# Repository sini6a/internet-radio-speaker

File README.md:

# Open Source Internet Radio Player

## Hardware Specifications

- **Microcontroller:** ESP32-C3
- **Power Supply:** 5V/0.5A (USB Type-C, ~2.5W)
- **Flash Memory:** 4Mbit QSPI (on-chip)
- **Antenna:** Integrated PCB antenna
- **Controls:** Power switch and analog volume potentiometer
- **Audio Output:** Dual speaker output (3.2W max per channel)
- **Indicators:** 3x LEDs (Wi-Fi, Playback, Power)

## Description

This project is a compact, ESP32-C3-based Internet Radio Player designed for ease of use and straightforward integration. The device supports Wi-Fi streaming of MP3 audio and includes basic control via a single potentiometer and button. Audio output is handled via I2S to a stereo amplifier. 

The hardware includes onboard status LEDs and is powered via USB Type-C. It's suitable for low-power audio streaming applications, DIY audio projects, or integration into custom enclosures.

## Features

- 2.4 GHz Wi-Fi support using the built-in PCB antenna
- Minimal controls for simple user interaction
- USB Type-C programming and power interface
- Stereo speaker output via digital I2S
- LED indicators for connection and playback status

## Firmware and Usage

The firmware is located in the `Firmware/` directory and is built using the Arduino framework. Upload it via the Arduino IDE or other compatible tools. 

### Initial Setup

1. Flash the firmware to the ESP32-C3.
2. On first boot, the device creates a Wi-Fi Access Point.
3. Connect to the AP to configure the Wi-Fi credentials and stream URL.
4. After setup, the device reboots into streaming mode.

## Status

- Current hardware revision is stable and has been tested.
- The device is functional and ready for personal assembly or integration.
- Further development (BLE config, web UI, OTA, etc.) is planned or ongoing.

## Contributions

Pull requests, issue reports, and improvements are welcome. Make sure to open issue before to discuss changes.

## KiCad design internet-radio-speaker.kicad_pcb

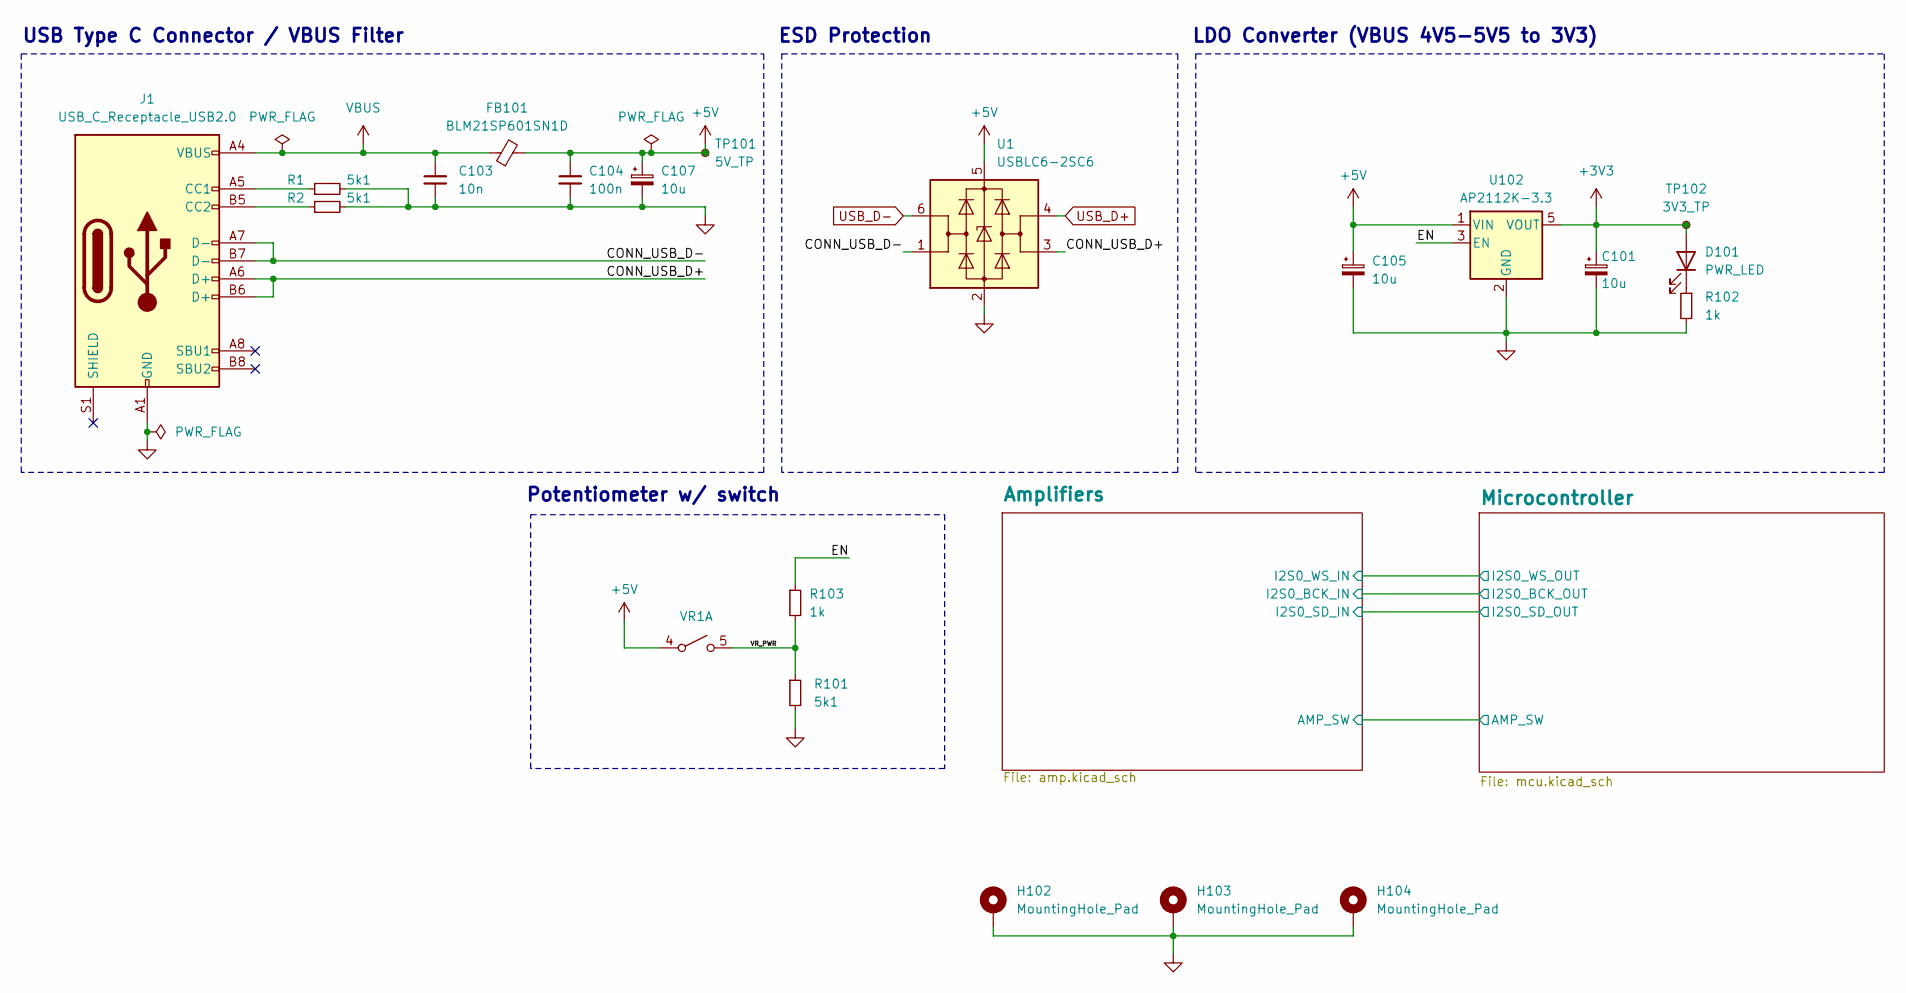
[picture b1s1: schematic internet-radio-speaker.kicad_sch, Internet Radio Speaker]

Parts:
C101, C105, C107: 10u; C_0603_1608Metric; JLCPCB Part # C96446
C103: 10n; C_0402_1005Metric; JLCPCB Part # C15195
C104: 100n; C_0402_1005Metric; JLCPCB Part # C1525
D101: PWR_LED; LED_0603_1608Metric; JLCPCB Part # C2286
FB101: BLM21SP601SN1D; L_0805_2012Metric; JLCPCB Part # C3716677
H102, H103, H104: MountingHole_Pad; MountingHole_2.7mm_M2.5_Pad_Via
J1: USB_C_Receptacle_USB2.0; USB_C_Receptacle_GCT_USB4105-xx-A_16P_TopMnt_Horizontal; JLCPCB Part # C2927038
R1, R2, R101: 5k1; R_0402_1005Metric; JLCPCB Part # C25905
R102, R103: 1k; R_0402_1005Metric; JLCPCB Part # C11702
TP101: 5V_TP; TestPoint_Pad_D1.5mm
TP102: 3V3_TP; TestPoint_Pad_D1.5mm
U1: USBLC6-2SC6; SOT-23-6; JLCPCB Part # C2687116
U102: AP2112K-3.3; SOT-23-5; JLCPCB Part # C51118
VR1: Potentiometer_Alps_RK0971111Z1P; JLCPCB Part # C2687318

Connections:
+3V3: C101.1, D101.2 (A), TP102.1, U102.5 (VOUT); also elsewhere on the board
+5V: C104.1, C105.1, C107.1, FB101.2, TP101.1, U1.5 (VBUS), U102.1 (VIN), VR1.4 (A); also elsewhere on the board
/CONN_USB_D+: J1.A6 (D+), J1.B6 (D+), U1.3 (I/O2)
/CONN_USB_D-: J1.A7 (D-), J1.B7 (D-), U1.1 (I/O1)
/EN: R103.1, U102.3 (EN)
/VR_PWR: R101.1, R103.2, VR1.5 (B)
GND: C101.2, C103.2, C104.2, C105.2, C107.2, H102.1, H103.1, H104.1, J1.A1 (GND), J1.A12 (GND), J1.B1 (GND), J1.B12 (GND), R1.2, R2.2, R101.2, R102.2, U1.2 (GND), U102.2 (GND); also elsewhere on the board
unnamed: D101.1 (K), R102.1
unnamed: J1.A5 (CC1), R1.1
unnamed: J1.B5 (CC2), R2.1
USB_D+: U1.4 (I/O2); also elsewhere on the board
USB_D-: U1.6 (I/O1); also elsewhere on the board
VBUS: C103.1, FB101.1, J1.A4 (VBUS), J1.A9 (VBUS), J1.B4 (VBUS), J1.B9 (VBUS)

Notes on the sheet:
ESD Protection
USB Type C Connector / VBUS Filter
Potentiometer w/ switch
LDO Converter (VBUS 4V5-5V5 to 3V3)

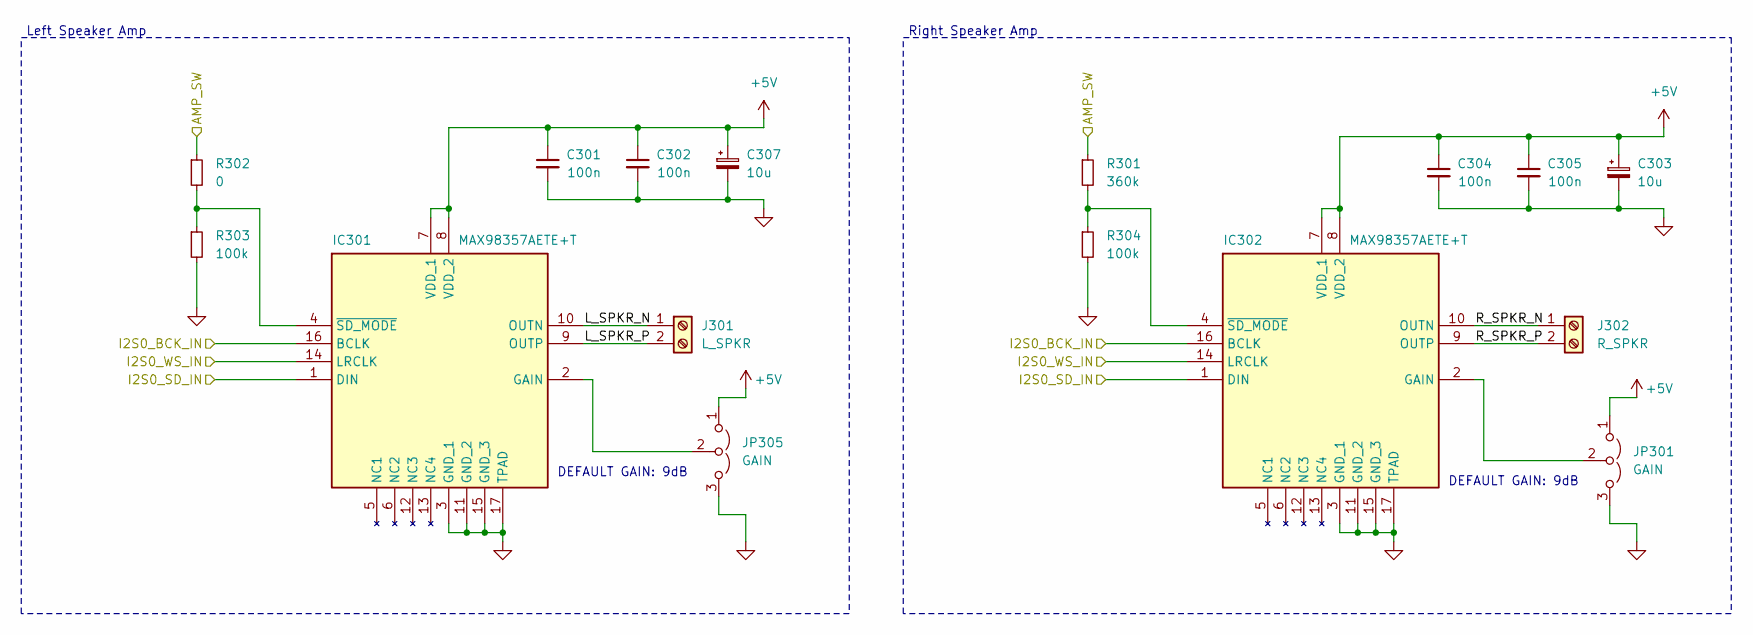
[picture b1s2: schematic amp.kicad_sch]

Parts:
C301, C302, C304, C305: 100n; C_0402_1005Metric; JLCPCB Part # C1525
C303, C307: 10u; C_0603_1608Metric; JLCPCB Part # C96446
IC301, IC302: MAX98357AETE+T; TQFN-16-1EP_3x3mm_P0.5mm_EP1.23x1.23mm_ThermalVias; JLCPCB Part # C910544
J301: L_SPKR; TerminalBlock_bornier-2_P5.08mm
J302: R_SPKR; TerminalBlock_bornier-2_P5.08mm
JP301, JP305: GAIN; SolderJumper-3_P1.3mm_Open_RoundedPad1.0x1.5mm
R301: 360k; R_0402_1005Metric; JLCPCB Part # C45956
R302: 0; R_0402_1005Metric; JLCPCB Part # C17168
R303, R304: 100k; R_0402_1005Metric; JLCPCB Part # C25741

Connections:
+5V: C301.1, C302.1, C303.1, C304.1, C305.1, C307.1, IC301.7 (VDD_1), IC301.8 (VDD_2), IC302.7 (VDD_1), IC302.8 (VDD_2), JP301.1 (A), JP305.1 (A); also elsewhere on the board
/Amplifiers/AMP_SW: R301.1, R302.1; also elsewhere on the board
/Amplifiers/I2S0_BCK_IN: IC301.16 (BCLK), IC302.16 (BCLK); also elsewhere on the board
/Amplifiers/I2S0_SD_IN: IC301.1 (DIN), IC302.1 (DIN); also elsewhere on the board
/Amplifiers/I2S0_WS_IN: IC301.14 (LRCLK), IC302.14 (LRCLK); also elsewhere on the board
/Amplifiers/L_SPKR_N: IC301.10 (OUTN), J301.1
/Amplifiers/L_SPKR_P: IC301.9 (OUTP), J301.2
/Amplifiers/R_SPKR_N: IC302.10 (OUTN), J302.1
/Amplifiers/R_SPKR_P: IC302.9 (OUTP), J302.2
GND: C301.2, C302.2, C303.2, C304.2, C305.2, C307.2, IC301.3 (GND_1), IC301.11 (GND_2), IC301.15 (GND_3), IC301.17 (TPAD), IC302.3 (GND_1), IC302.11 (GND_2), IC302.15 (GND_3), IC302.17 (TPAD), JP301.3 (B), JP305.3 (B), R303.2, R304.2; also elsewhere on the board
unnamed: IC301.2 (GAIN), JP305.2 (C)
unnamed: IC301.4 (~SD_MODE), R302.2, R303.1
unnamed: IC302.2 (GAIN), JP301.2 (C)
unnamed: IC302.4 (~SD_MODE), R301.2, R304.1

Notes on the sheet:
Left Speaker Amp
Right Speaker Amp
DEFAULT GAIN: 9dB

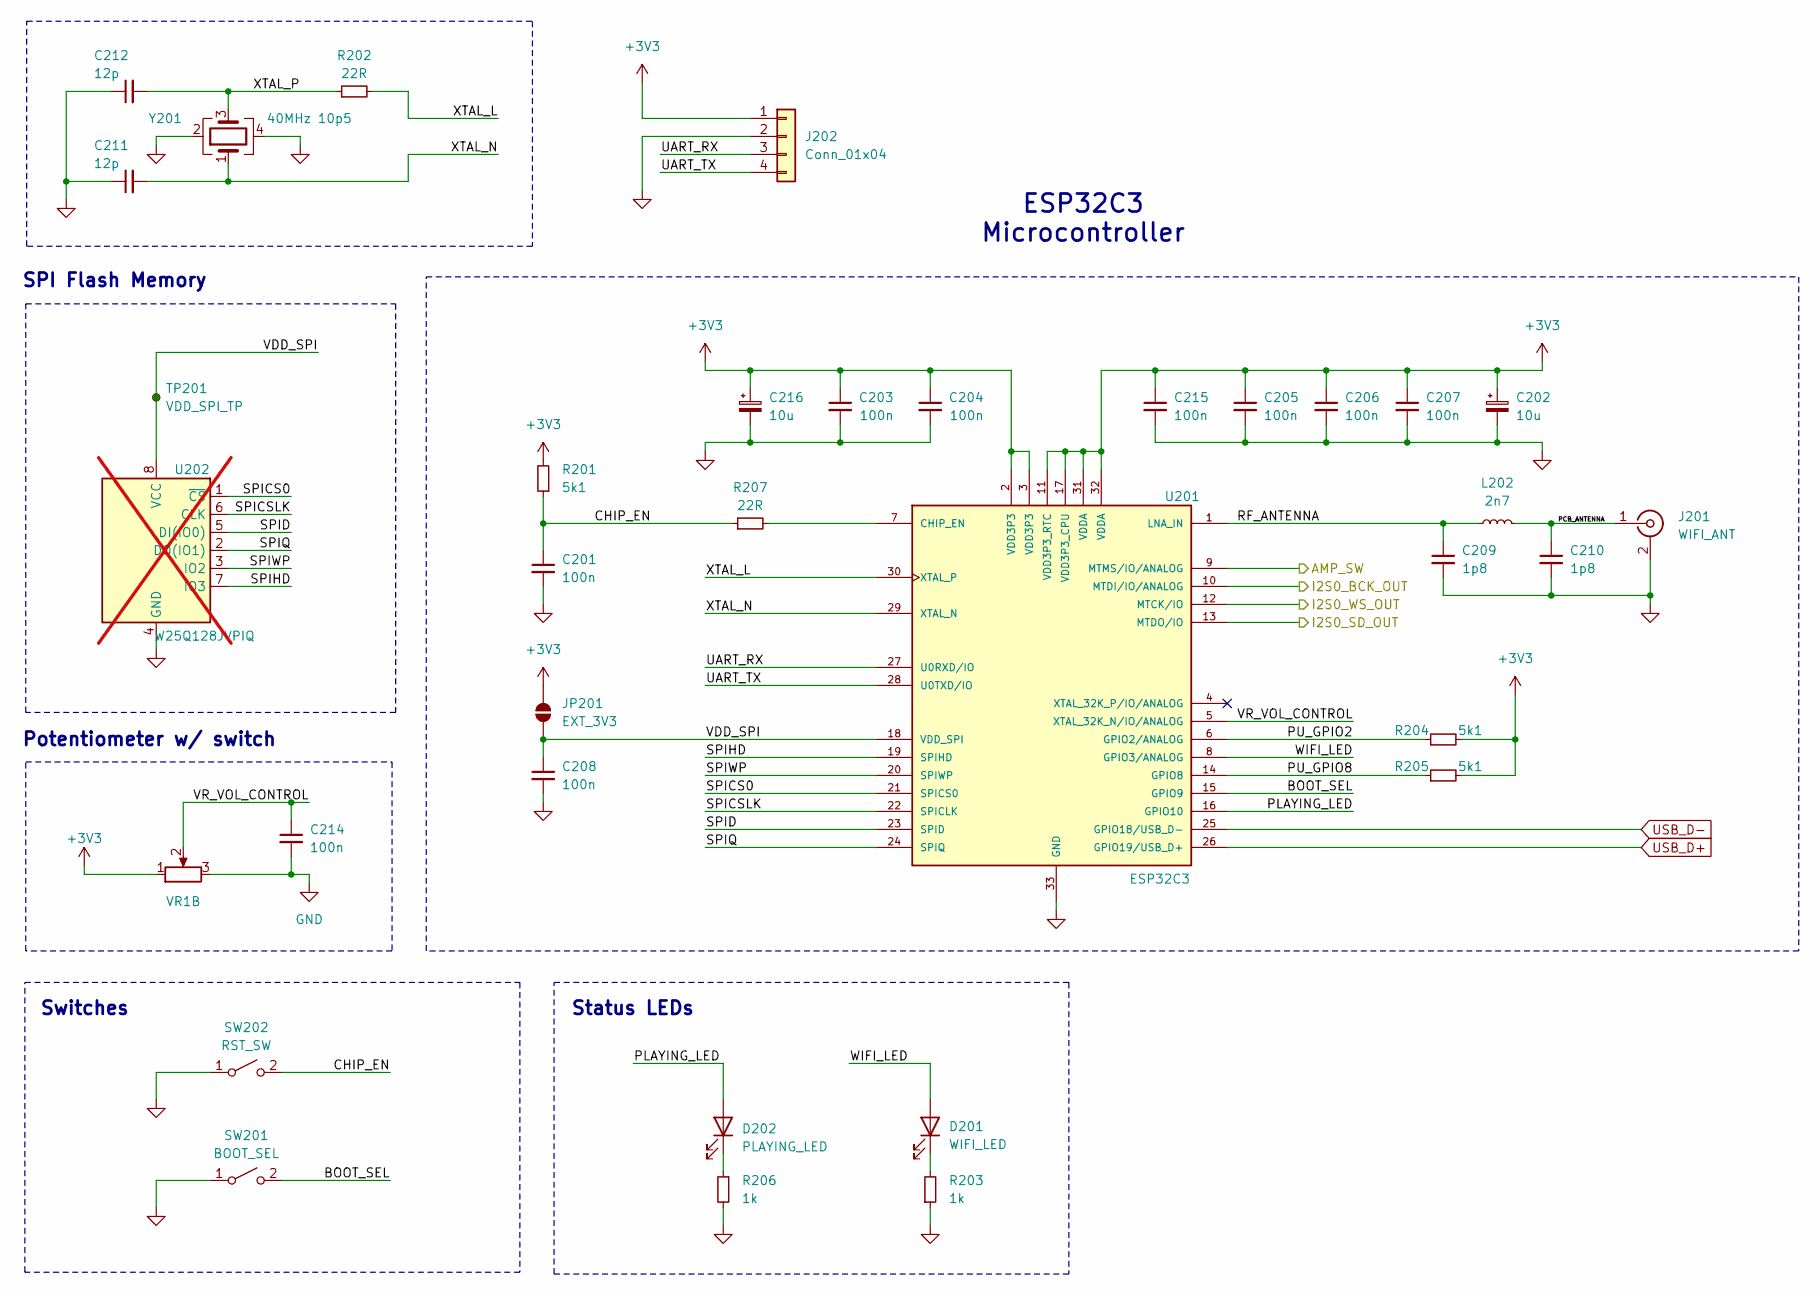
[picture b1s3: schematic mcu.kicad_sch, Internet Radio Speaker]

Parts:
C201, C203, C204, C205, C206, C207, C208, C214, C215: 100n; C_0402_1005Metric; JLCPCB Part # C1525
C202, C216: 10u; C_0603_1608Metric; JLCPCB Part # C96446
C209, C210: 1p8; C_0402_1005Metric; JLCPCB Part # C1553
C211, C212: 12p; C_0402_1005Metric; JLCPCB Part # C1547
D201: WIFI_LED; LED_0805_2012Metric; JLCPCB Part # C2297
D202: PLAYING_LED; LED_0805_2012Metric; JLCPCB Part # C2296
J201: WIFI_ANT; Texas_SWRA117D_2.4GHz_Right; LCSC C3174435
J202: Conn_01x04; PinSocket_1x04_P2.54mm_Vertical
JP201: EXT_3V3; SolderJumper-2_P1.3mm_Open_RoundedPad1.0x1.5mm
L202: 2n7; L_0402_1005Metric; JLCPCB Part # C77108
R201, R204, R205: 5k1; R_0402_1005Metric; JLCPCB Part # C25905
R202, R207: 22R; R_0402_1005Metric; JLCPCB Part # C25092
R203, R206: 1k; R_0402_1005Metric; JLCPCB Part # C11702
SW201: BOOT_SEL; SW_PUSH_6mm; JLCPCB Part # C2889001
SW202: RST_SW; SW_PUSH_6mm; JLCPCB Part # C2889001
TP201: VDD_SPI_TP; TestPoint_Pad_D1.5mm
U201: ESP32C3; HVQFN-32-1EP_5x5mm_P0.5mm_EP3.1x3.1mm_ThermalVias; LCSC C2858491
U202: W25Q128JVPIQ; WSON-8-1EP_6x5mm_P1.27mm_EP3.4x4.3mm; JLCPCB Part # C190862; not fitted
VR1: Potentiometer_Alps_RK0971111Z1P; JLCPCB Part # C2687318
Y201: 40MHz 10p5; Crystal_SMD_3225-4Pin_3.2x2.5mm; JLCPCB Part # C19191260

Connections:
+3V3: C202.1, C203.1, C204.1, C205.1, C206.1, C207.1, C215.1, C216.1, J202.1, JP201.2 (B), R201.2, R204.2, R205.2, U201.2 (VDD3P3), U201.3 (VDD3P3), U201.11 (VDD3P3_RTC), U201.17 (VDD3P3_CPU), U201.31 (VDDA), U201.32 (VDDA), VR1.1; also elsewhere on the board
/Amplifiers/AMP_SW: U201.9 (MTMS/IO/ANALOG); also elsewhere on the board
/Amplifiers/I2S0_BCK_IN: U201.10 (MTDI/IO/ANALOG); also elsewhere on the board
/Amplifiers/I2S0_SD_IN: U201.13 (MTDO/IO); also elsewhere on the board
/Amplifiers/I2S0_WS_IN: U201.12 (MTCK/IO); also elsewhere on the board
/Microcontroller/BOOT_SEL: SW201.2 (B), U201.15 (GPIO9)
/Microcontroller/CHIP_EN: C201.1, R201.1, R207.1, SW202.2 (B)
/Microcontroller/PCB_ANTENNA: C210.1, J201.1 (In), L202.2
/Microcontroller/PLAYING_LED: D202.2 (A), U201.16 (GPIO10)
/Microcontroller/PU_GPIO2: R204.1, U201.6 (GPIO2/ANALOG)
/Microcontroller/PU_GPIO8: R205.1, U201.14 (GPIO8)
/Microcontroller/RF_ANTENNA: C209.1, L202.1, U201.1 (LNA_IN)
/Microcontroller/SPICS0: U201.21 (SPICS0), U202.1 (~CS)
/Microcontroller/SPICSLK: U201.22 (SPICLK), U202.6 (CLK)
/Microcontroller/SPID: U201.23 (SPID), U202.5 (DI(IO0))
/Microcontroller/SPIHD: U201.19 (SPIHD), U202.7 (IO3)
/Microcontroller/SPIQ: U201.24 (SPIQ), U202.2 (DO(IO1))
/Microcontroller/SPIWP: U201.20 (SPIWP), U202.3 (IO2)
/Microcontroller/UART_RX: J202.3, U201.27 (U0RXD/IO)
/Microcontroller/UART_TX: J202.4, U201.28 (U0TXD/IO)
/Microcontroller/VDD_SPI: C208.1, JP201.1 (A), TP201.1, U201.18 (VDD_SPI), U202.8 (VCC)
/Microcontroller/VR_VOL_CONTROL: C214.1, U201.5 (XTAL_32K_N/IO/ANALOG), VR1.2
/Microcontroller/WIFI_LED: D201.2 (A), U201.8 (GPIO3/ANALOG)
/Microcontroller/XTAL_L: R202.2, U201.30 (XTAL_P)
/Microcontroller/XTAL_N: C211.2, U201.29 (XTAL_N), Y201.1
/Microcontroller/XTAL_P: C212.2, R202.1, Y201.3
GND: C201.2, C202.2, C203.2, C204.2, C205.2, C206.2, C207.2, C208.2, C209.2, C210.2, C211.1, C212.1, C214.2, C215.2, C216.2, J201.2 (Ext), J202.2, R203.1, R206.2, SW201.1 (A), SW202.1 (A), U201.33 (GND), U202.4 (GND), VR1.3, Y201.2, Y201.4; also elsewhere on the board
unnamed: D201.1 (K), R203.2
unnamed: D202.1 (K), R206.1
unnamed: R207.2, U201.7 (CHIP_EN)
USB_D+: U201.26 (GPIO19/USB_D+); also elsewhere on the board
USB_D-: U201.25 (GPIO18/USB_D-); also elsewhere on the board

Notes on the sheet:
SPI Flash Memory
Status LEDs
Potentiometer w/ switch
Switches
ESP32C3 Microcontroller

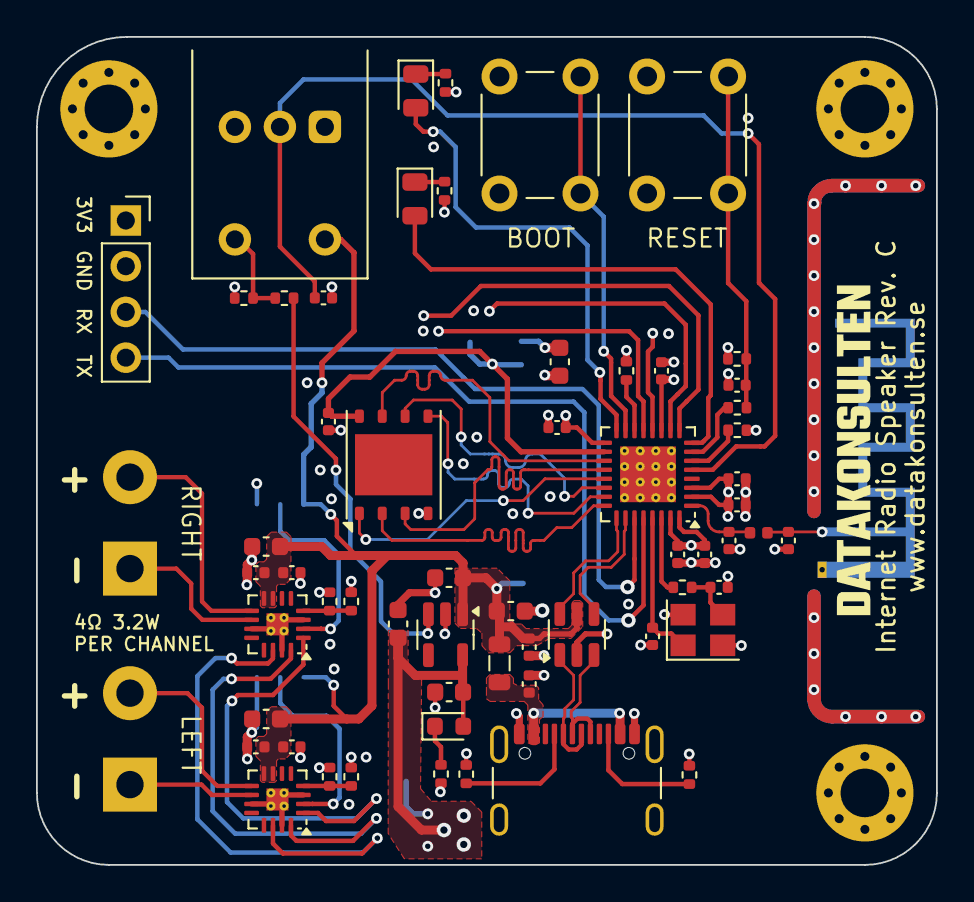
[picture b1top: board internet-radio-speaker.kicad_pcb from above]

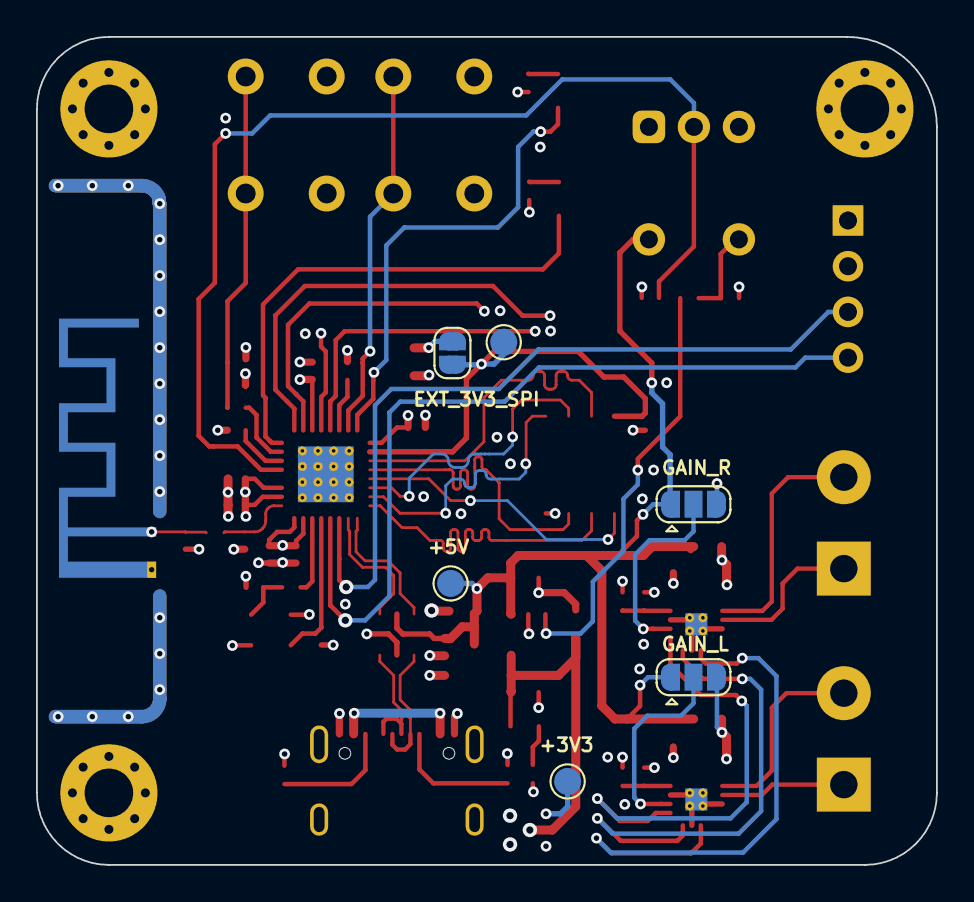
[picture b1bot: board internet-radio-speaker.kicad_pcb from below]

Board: 4 copper layers, 50.0 x 46.0 mm, 71 parts (7 on the bottom side), 49 nets.

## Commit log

2024-01-07 Added potentiometer and fixed amplifiers
2024-01-24 Finished rev 1 of the board
2024-01-25 added screenshots, added readme and licence
2024-01-25 updated typo
2024-09-24 updated to rev 3
2025-05-07 updated to rev 4
2025-05-07 added firmware file for arduino
2025-05-07 updated readme.md and pictures rev 4
2025-05-07 Updated to KiCad 9
2026-06-30 added schematic pdf
